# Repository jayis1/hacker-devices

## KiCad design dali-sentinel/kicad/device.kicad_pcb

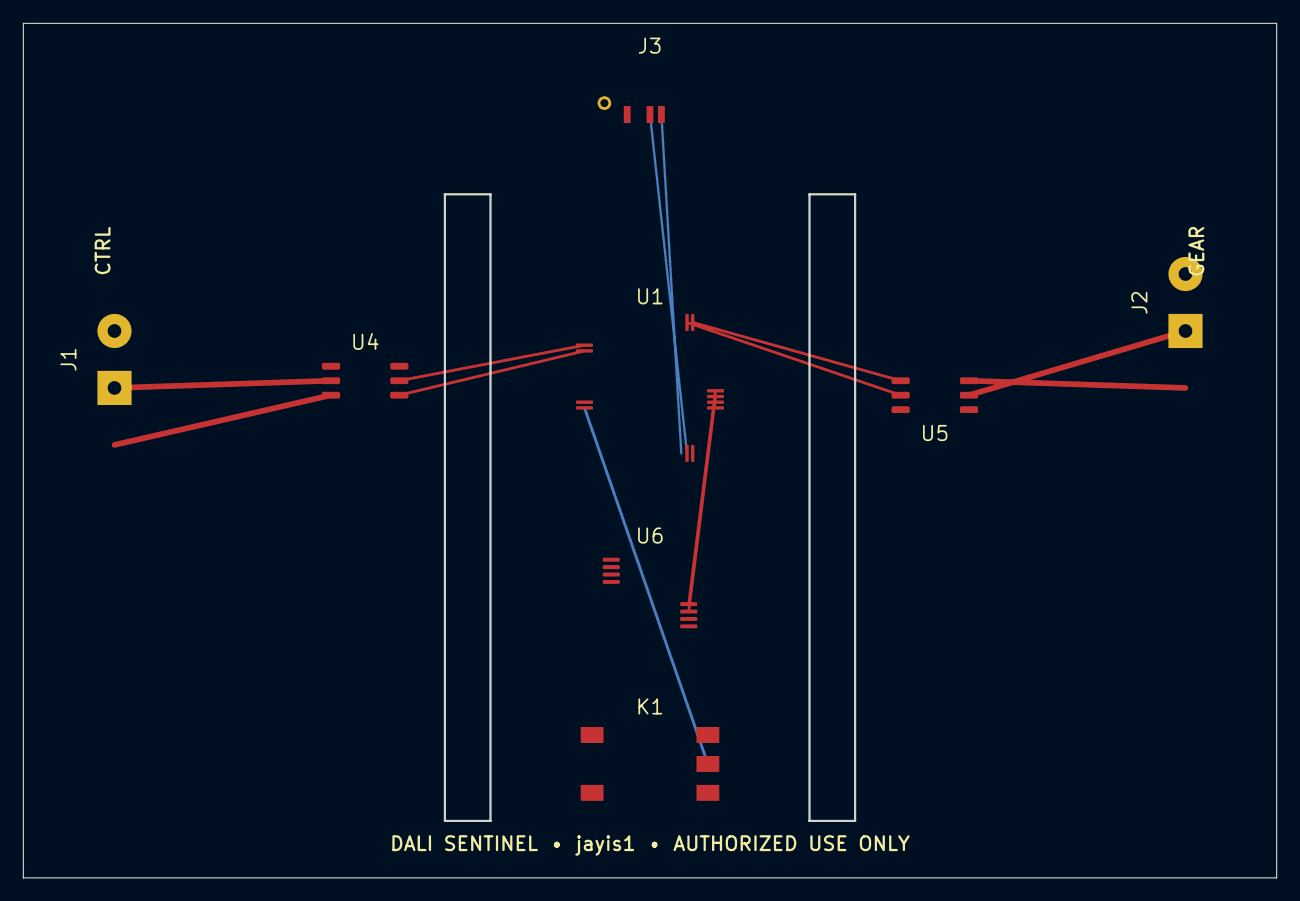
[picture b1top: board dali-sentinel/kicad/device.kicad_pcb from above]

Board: 4 copper layers, 110.0 x 75.0 mm, 8 parts (0 on the bottom side), 17 nets.

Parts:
J1: DALI CTRL; TerminalBlock_Phoenix_MKDS-1,5-2_1x02_P5.00mm_Horizontal
J2: DALI GEAR; TerminalBlock_Phoenix_MKDS-1,5-2_1x02_P5.00mm_Horizontal
J3: USB-C; USB_C_Receptacle_GCT_USB4105-xx-A_16P_TopMnt_Horizontal
K1: NC FAILSAFE BYPASS; Relay_DPDT_Omron_G6K-2F-Y
U1: STM32G474RET6; LQFP-64_10x10mm_P0.5mm
U4: ISO7721 CTRL; SOIC-8_3.9x4.9mm_P1.27mm
U5: ISO7721 GEAR; SOIC-8_3.9x4.9mm_P1.27mm
U6: ADS131M04; TSSOP-20_4.4x6.5mm_P0.65mm

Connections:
+3V3: U1.63, U4.8, U5.8
ADC_CS: U1.28, U6.18
ADC_SPI_MISO: U1.26, U6.16
ADC_SPI_MOSI: U1.27, U6.17
ADC_SPI_SCK: U1.25, U6.15
BYPASS_CTL: K1.4, U1.45
DALI_CTRL_A: J1.1, K1.1, U4.2, U6.1
DALI_CTRL_B: J1.2, K1.2, U4.3, U6.2
DALI_GEAR_A: J2.1, K1.8, U5.2, U6.3
DALI_GEAR_B: J2.2, K1.7, U5.3, U6.4
GND: J3.A1, U1.64
RX_CTRL_ISO: U1.1, U4.7
RX_GEAR_ISO: U1.15, U5.7
TX_CTRL_ISO: U1.2, U4.6
TX_GEAR_ISO: U1.16, U5.6
USB_DM: J3.A7, U1.34
USB_DP: J3.A6, U1.33

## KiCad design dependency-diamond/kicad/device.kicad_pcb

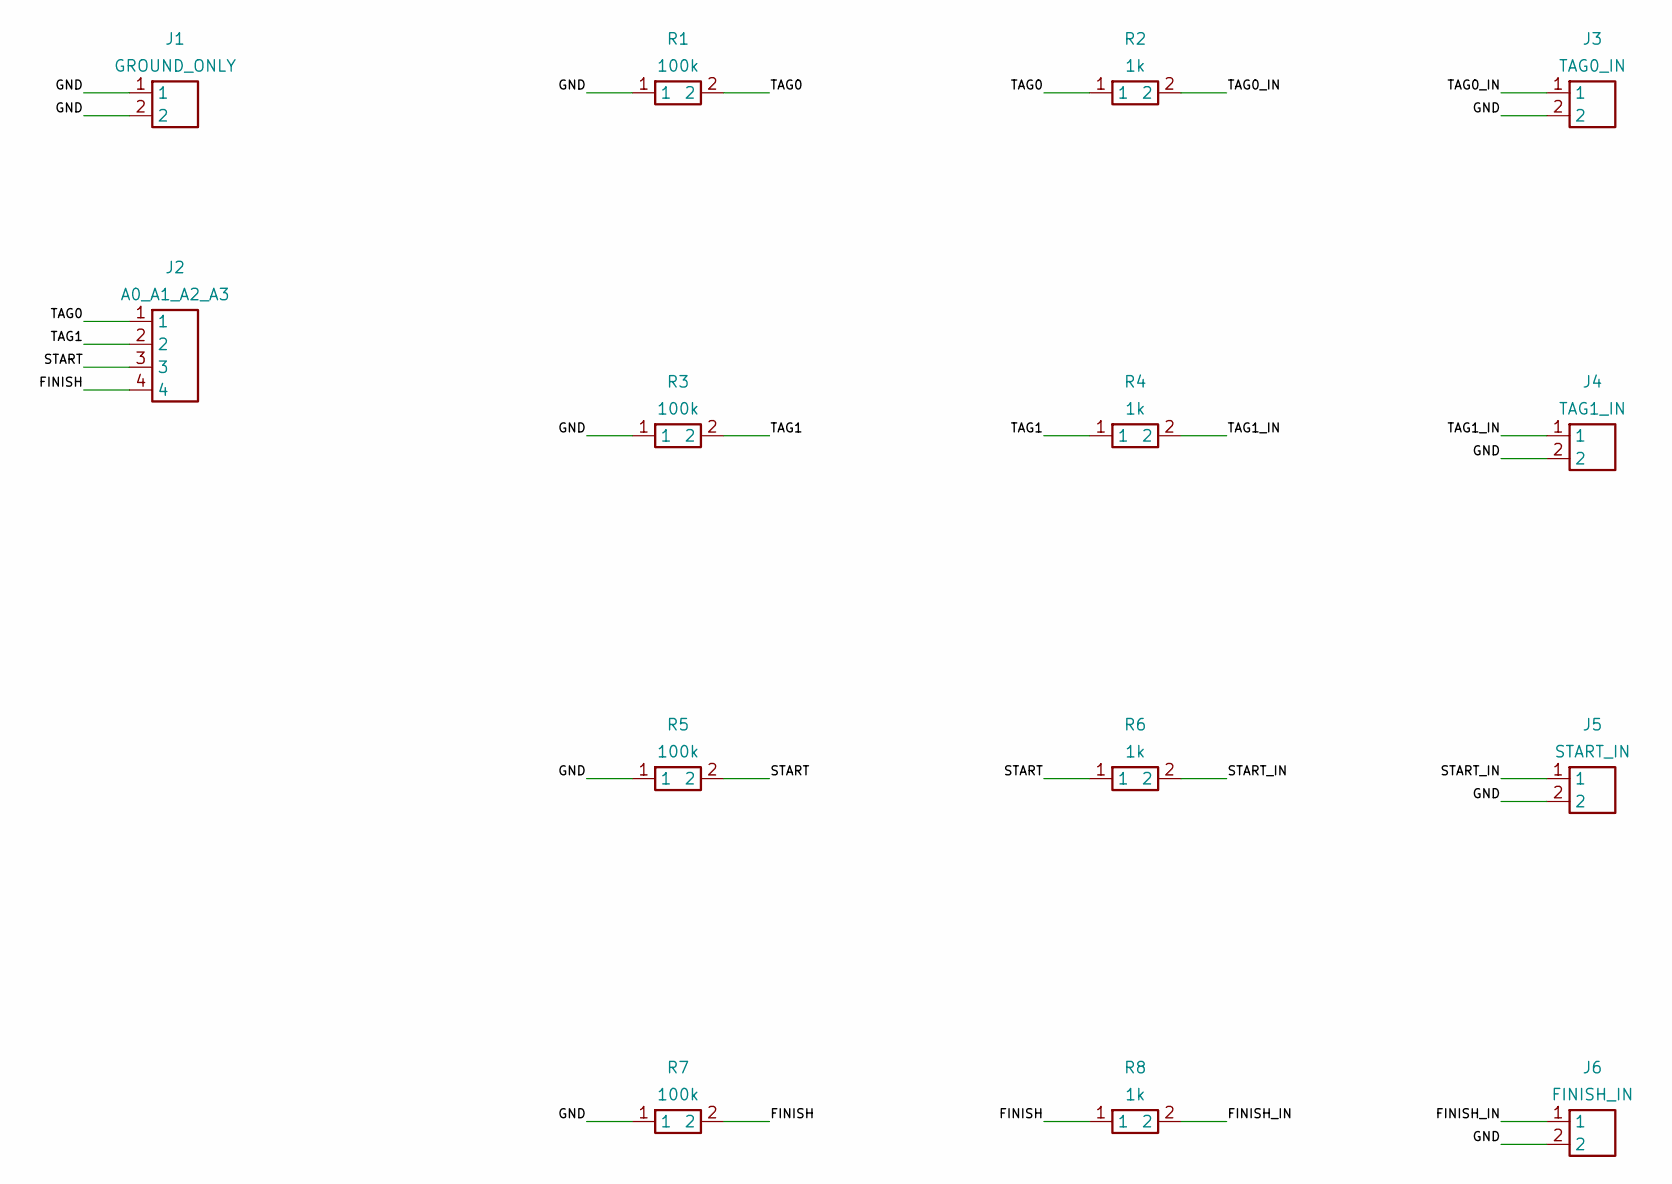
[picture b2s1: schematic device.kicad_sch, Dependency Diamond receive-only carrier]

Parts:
J1: GROUND_ONLY; PinHeader_1x02_P2.54mm_Vertical
J2: A0_A1_A2_A3; PinHeader_1x04_P2.54mm_Vertical
J3: TAG0_IN; PinHeader_1x02_P2.54mm_Vertical
J4: TAG1_IN; PinHeader_1x02_P2.54mm_Vertical
J5: START_IN; PinHeader_1x02_P2.54mm_Vertical
J6: FINISH_IN; PinHeader_1x02_P2.54mm_Vertical
R1, R3, R5, R7: 100k; R_Axial_DIN0207_L6.3mm_D2.5mm_P7.62mm_Horizontal
R2, R4, R6, R8: 1k; R_Axial_DIN0207_L6.3mm_D2.5mm_P7.62mm_Horizontal

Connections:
FINISH: J2.4, R7.2, R8.1
FINISH_IN: J6.1, R8.2
GND: J1.1, J1.2, J3.2, J4.2, J5.2, J6.2, R1.1, R3.1, R5.1, R7.1
START: J2.3, R5.2, R6.1
START_IN: J5.1, R6.2
TAG0: J2.1, R1.2, R2.1
TAG0_IN: J3.1, R2.2
TAG1: J2.2, R3.2, R4.1
TAG1_IN: J4.1, R4.2

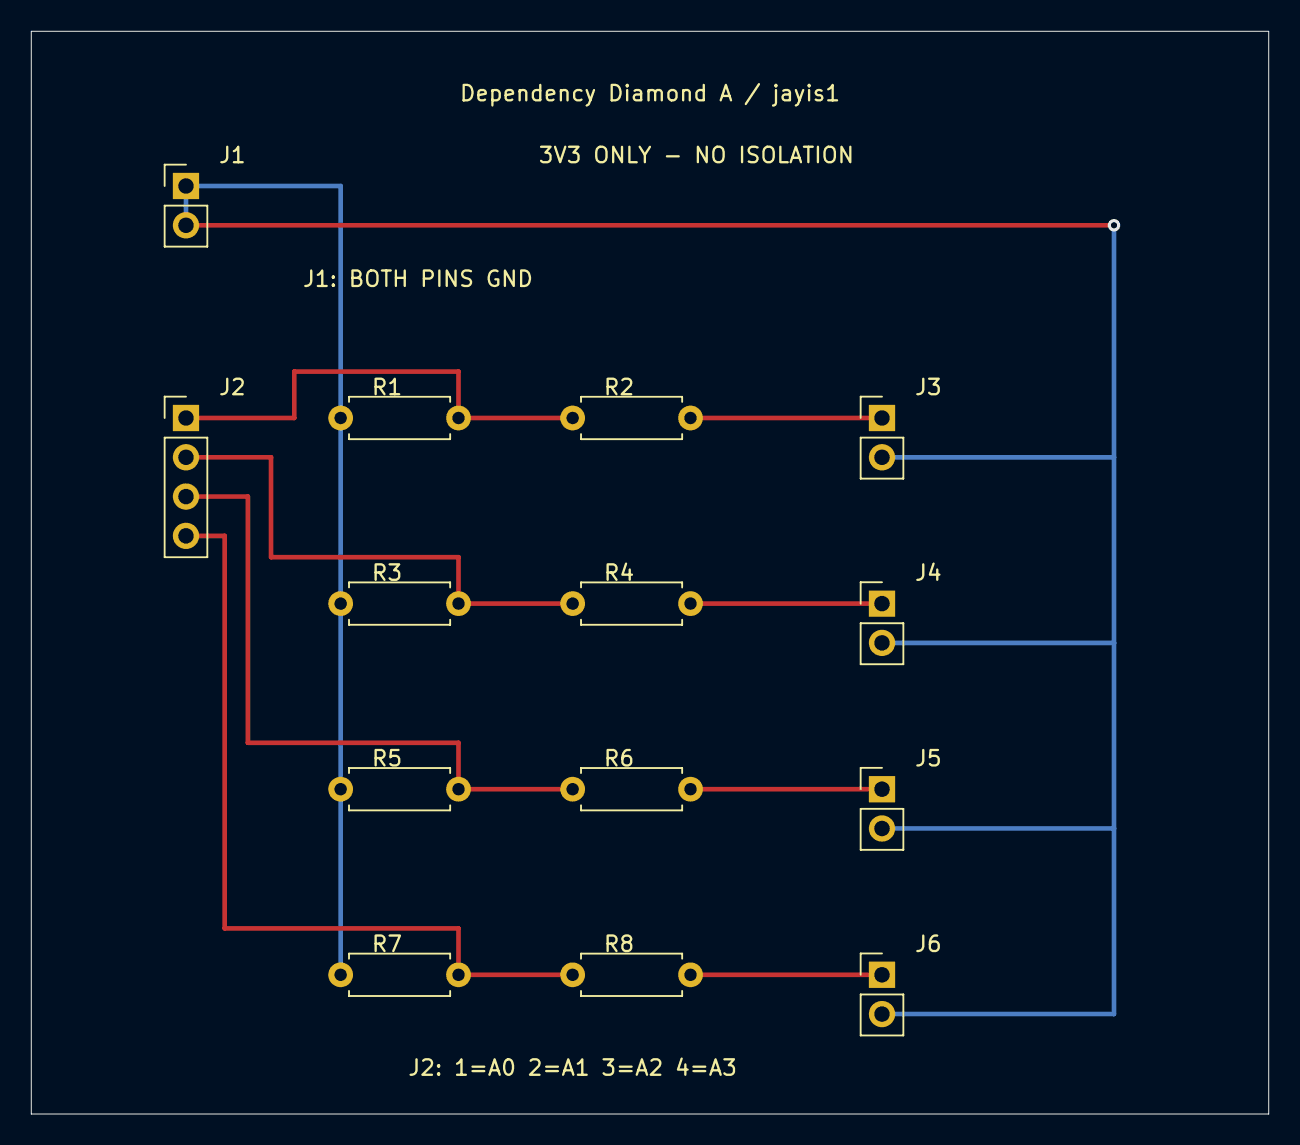
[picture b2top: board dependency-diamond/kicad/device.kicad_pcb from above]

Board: 2 copper layers, 80.0 x 70.0 mm, 14 parts (0 on the bottom side), 9 nets.

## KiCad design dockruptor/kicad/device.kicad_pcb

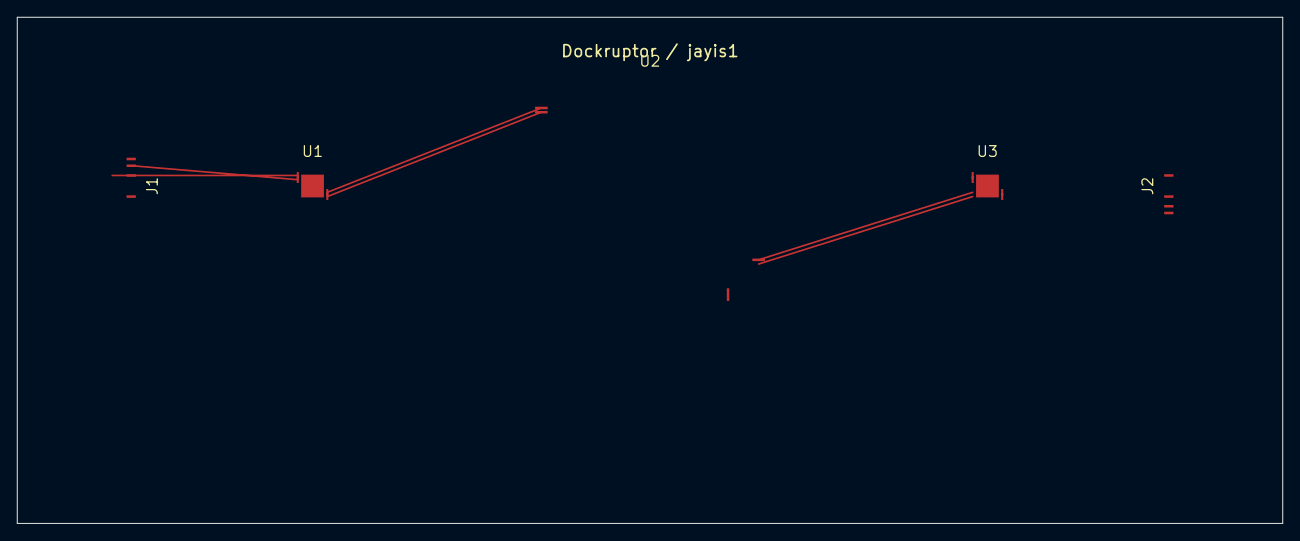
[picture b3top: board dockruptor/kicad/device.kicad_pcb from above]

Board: 2 copper layers, 150.0 x 60.0 mm, 5 parts (0 on the bottom side), 8 nets.

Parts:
J1: USB_C_HOST; USB_C_Receptacle_GCT_USB4105-xx-A_16P_TopMnt_Horizontal
J2: USB_C_DOCK; USB_C_Receptacle_GCT_USB4105-xx-A_16P_TopMnt_Horizontal
U1: FUSB307B_A; QFN-24-1EP_4x4mm_P0.5mm_EP2.7x2.7mm
U2: STM32H735IGK6; LQFP-176_24x24mm_P0.5mm
U3: FUSB307B_B; QFN-24-1EP_4x4mm_P0.5mm_EP2.7x2.7mm

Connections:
CC1_DOCK: J2.A5, U3.1
CC1_HOST: J1.A5, U1.1
CC2_DOCK: J2.B5, U3.2
CC2_HOST: J1.B5, U1.2
GND: J1.A1, J2.A1, U1.25, U2.89, U3.25
I2C_SCL: U1.23, U2.12, U3.23
I2C_SDA: U1.24, U2.13, U3.24
VBUS_MAIN: J1.A4, J2.A4

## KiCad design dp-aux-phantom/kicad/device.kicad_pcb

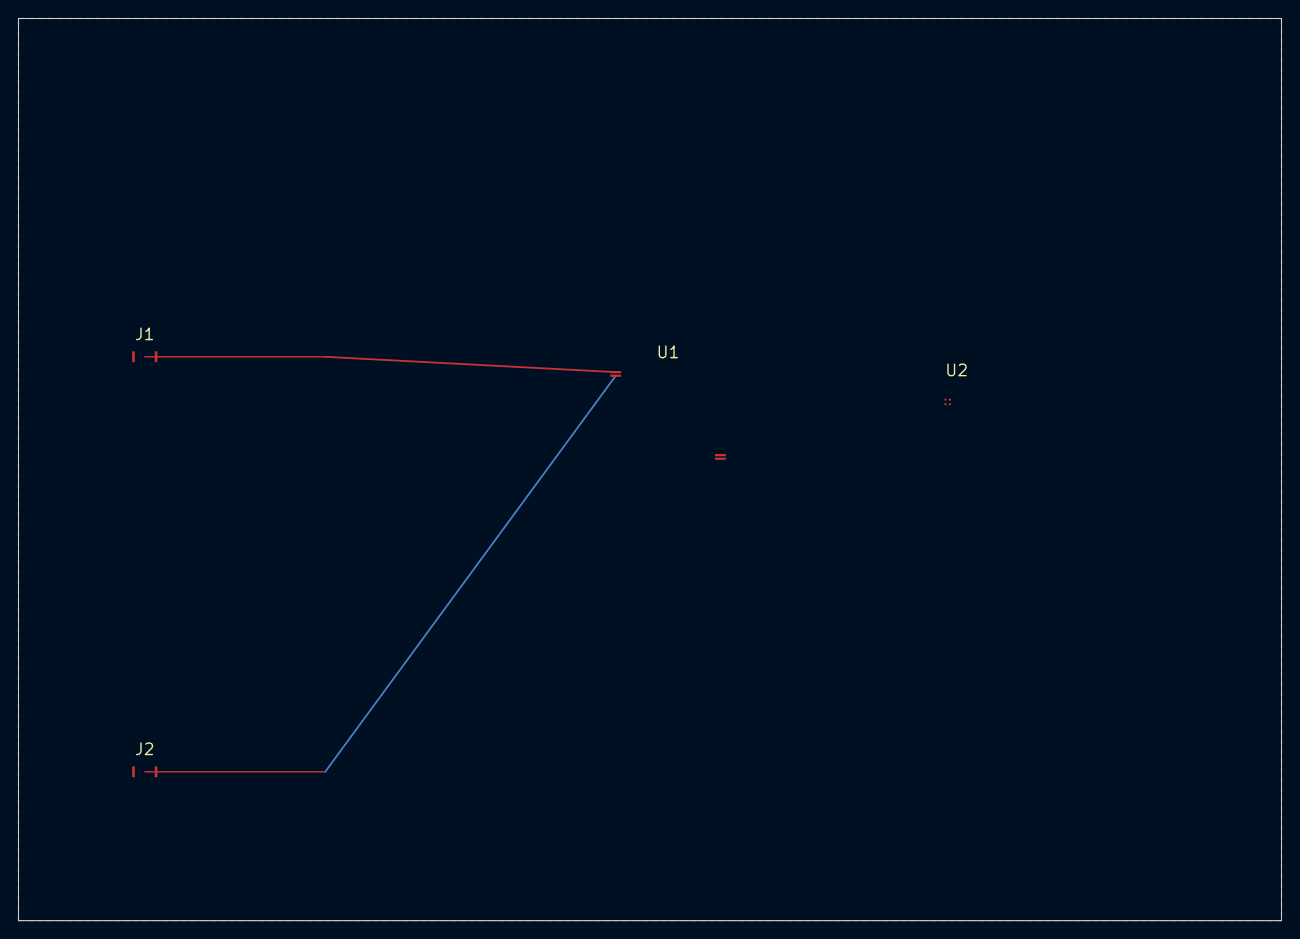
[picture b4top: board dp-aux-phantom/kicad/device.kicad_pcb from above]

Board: 2 copper layers, 140.0 x 100.0 mm, 4 parts (0 on the bottom side), 2 nets.

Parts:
J1: USB-C_HOST; USB_C_Receptacle_HRO_TYPE-C-31-M-12
J2: USB-C_SINK; USB_C_Receptacle_HRO_TYPE-C-31-M-12
U1: RP2350B; TQFP-80_10x10mm_P0.4mm
U2: iCE40UP5K; ucBGA-48_3.65x3.65mm_Layout6x8_P0.5mm

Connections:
SCL_CTRL: J1.A5, J2.A5, U1.1
SDA_CTRL: J1.B5, J2.B5, U1.2

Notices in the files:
dram-phantom/kicad/device.kicad_sch:
License: CERN-OHL-S v2
